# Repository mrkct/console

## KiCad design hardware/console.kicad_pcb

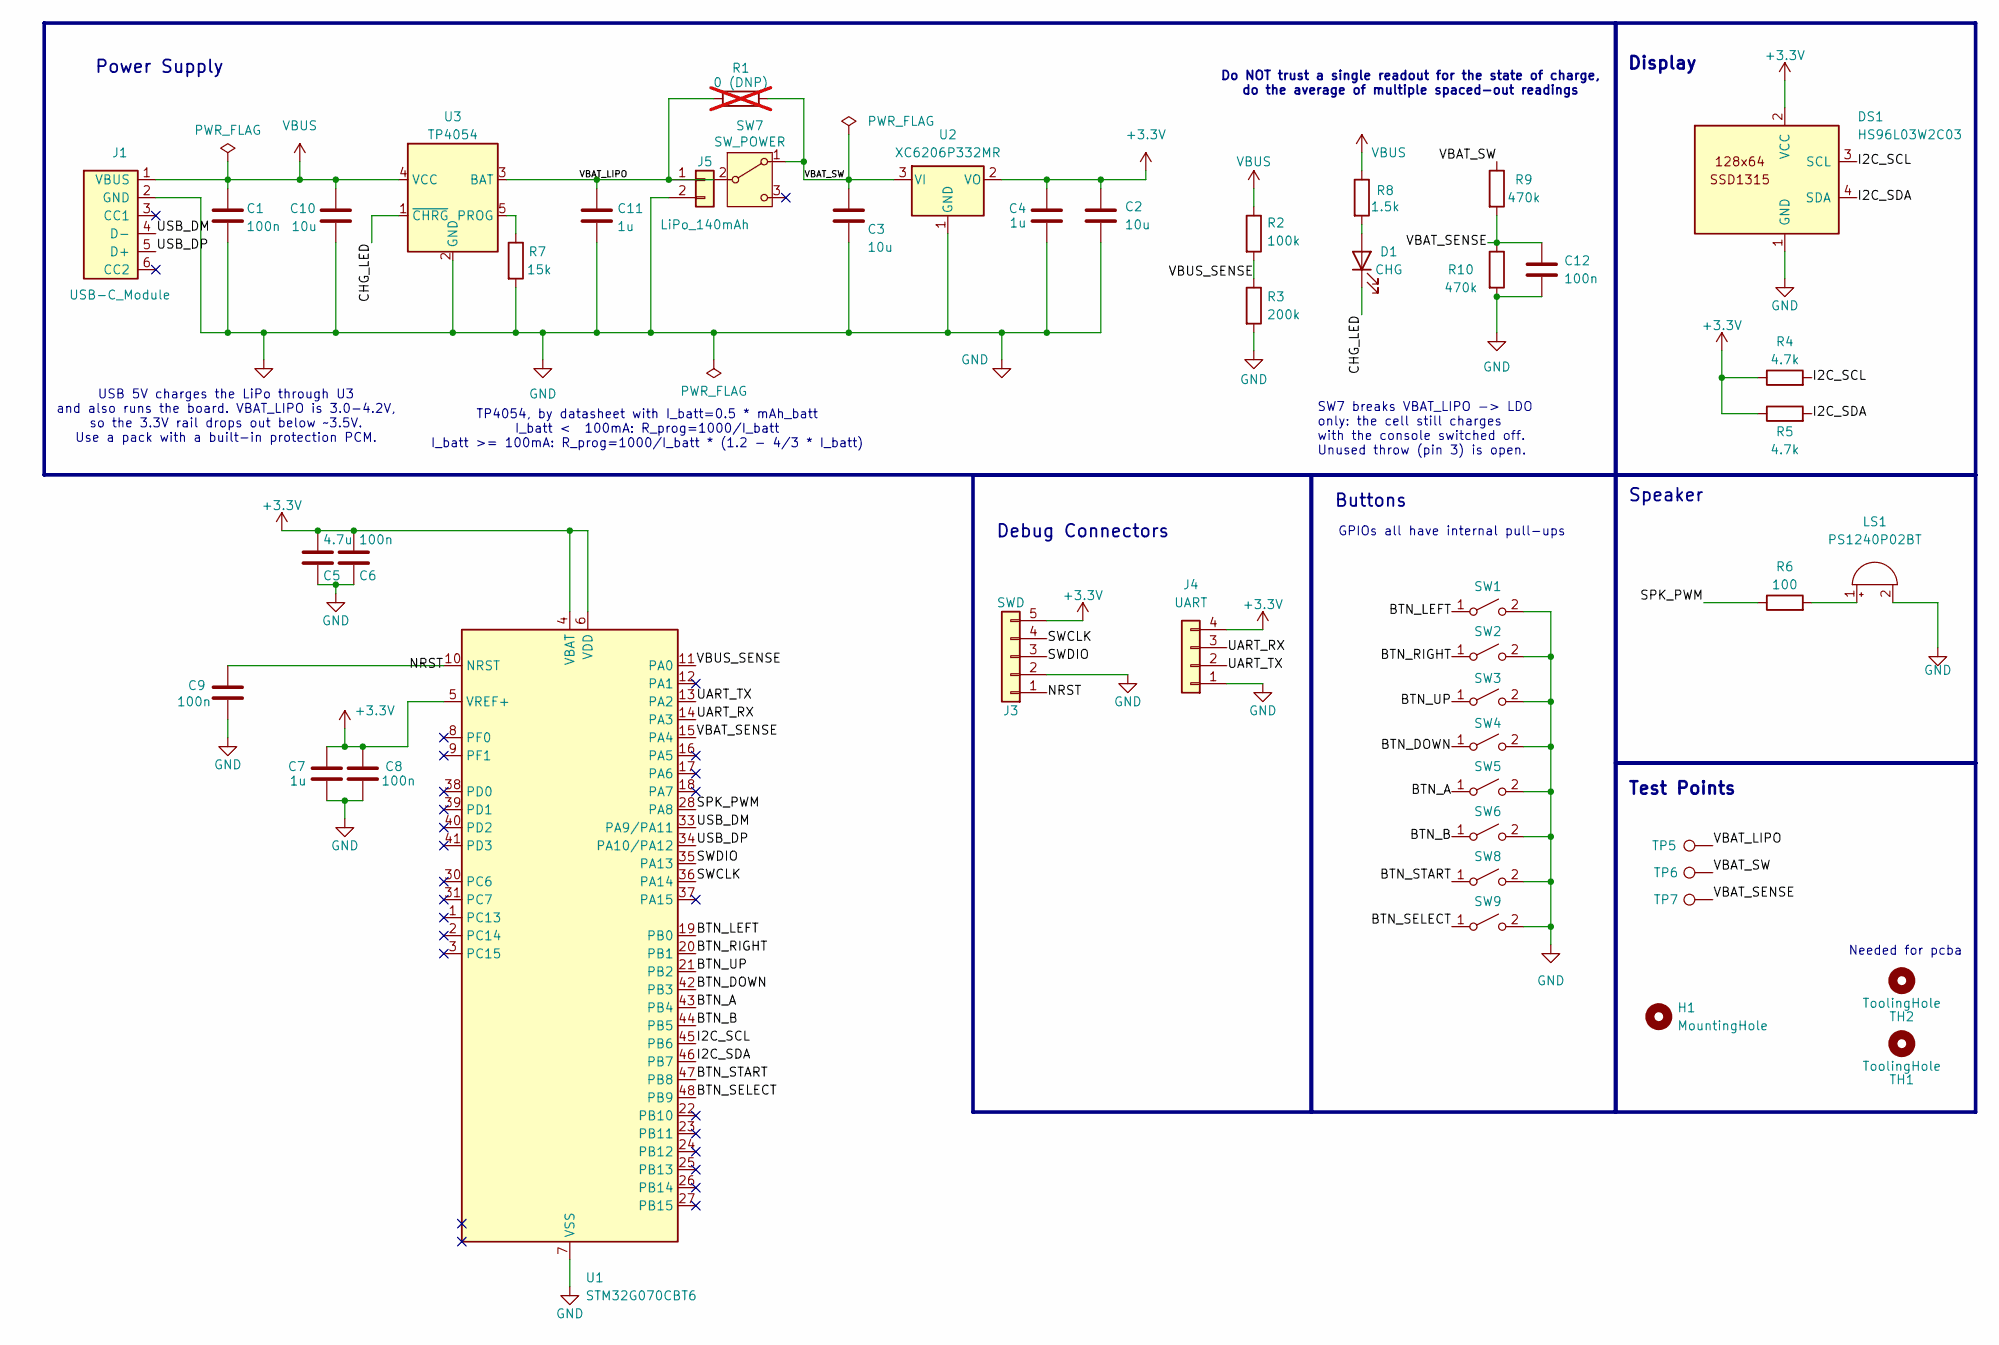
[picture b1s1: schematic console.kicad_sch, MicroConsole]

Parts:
C1, C6, C8, C9, C12: 100n; C_0402_1005Metric; Voltage 16V; MPN CL05B104KO5NNNC; LCSC C1525
C2, C3, C10: 10u; C_0805_2012Metric; Voltage 25V; MPN CL21A106KAYNNNE; LCSC C15850
C4, C7, C11: 1u; C_0402_1005Metric; Voltage 25V; MPN CL05A105KA5NQNC; LCSC C52923
C5: 4.7u; C_0603_1608Metric; Voltage 16V; MPN CL10A475KO8NNNC; LCSC C19666
D1: CHG; LED_0603_1608Metric; MPN KT-0603R; LCSC C2286
DS1: HS96L03W2C03; OLED-TH_L27.8-W27.2-P2.54_C9900033791; LCSC C5248080
H1: MountingHole; MountingHole_2.1mm
J1: USB-C_Module; USBC-TH_L21.6-W12.8-P2.54
J3: SWD; PinHeader_1x05_P2.54mm_Vertical
J4: UART; PinHeader_1x04_P2.54mm_Vertical
J5: LiPo_140mAh; JST_PH_S2B-PH-K_1x02_P2.00mm_Horizontal; MPN BX-PH2.0-2PZZ; LCSC C18077744
LS1: PS1240P02BT; Buzzer_TDK_PS1240P02BT_D12.2mm_H6.5mm; MPN PS1240P02BT; LCSC C76871
R1: 0 (DNP); R_0402_1005Metric; not fitted
R2: 100k; R_0402_1005Metric; Tolerance 1%; MPN 0402WGF1003TCE; LCSC C25741
R3: 200k; R_0402_1005Metric; Tolerance 1%; MPN 0402WGF2003TCE; LCSC C25764
R4, R5: 4.7k; R_0402_1005Metric; Tolerance 1%; MPN 0402WGF4701TCE; LCSC C25900
R6: 100; R_0402_1005Metric; Tolerance 1%; MPN 0402WGF1000TCE; LCSC C25076
R7: 15k; R_0402_1005Metric; Tolerance 1%; MPN 0402WGF1502TCE; LCSC C25756
R8: 1.5k; R_0402_1005Metric; Tolerance 1%; MPN 0402WGF1501TCE; LCSC C25867
R9, R10: 470k; R_0603_1608Metric; Tolerance 1%; MPN 0603WAF4703T5E; LCSC C23178
SW1, SW2, SW3, SW4, SW5, SW6, SW8, SW9: SW_PUSH; SW_SPST_TS-1088-xR020; LCSC C720477
SW7: SW_POWER; SW-TH_L8.5-W3.5-P2.50-D0.9; MPN SS-12D00
TH1, TH2: ToolingHole; TOOL-NPTH-D1.152
TP5: VBAT_LIPO; TestPoint_THTPad_D1.5mm_Drill0.7mm
TP6: VBAT_SW; TestPoint_THTPad_D1.5mm_Drill0.7mm
TP7: VBAT_SENSE; TestPoint_THTPad_D1.5mm_Drill0.7mm
U1: STM32G070CBT6; LQFP-48_7x7mm_P0.5mm; MPN STM32G070CBT6; LCSC C529338
U2: XC6206P332MR; SOT-23-3; MPN XC6206P332MR-G; LCSC C5446
U3: TP4054; SOT-23-5; MPN TP4054-42-SOT25R; LCSC C32574

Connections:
+3.3V: C2.1, C4.1, C5.1, C6.1, C7.1, C8.1, DS1.2 (VCC), J3.5, J4.4, R4.1, R5.1, U1.4 (VBAT), U1.5 (VREF+), U1.6 (VDD), U2.2 (VO)
/BTN_A: SW5.1 (A), U1.43 (PB4)
/BTN_B: SW6.1 (A), U1.44 (PB5)
/BTN_DOWN: SW4.1 (A), U1.42 (PB3)
/BTN_LEFT: SW1.1 (A), U1.19 (PB0)
/BTN_RIGHT: SW2.1 (A), U1.20 (PB1)
/BTN_SELECT: SW9.1 (A), U1.48 (PB9)
/BTN_START: SW8.1 (A), U1.47 (PB8)
/BTN_UP: SW3.1 (A), U1.21 (PB2)
/CHG_LED: D1.1 (K), U3.1 (~CHRG)
/I2C_SCL: DS1.3 (SCL), R4.2, U1.45 (PB6)
/I2C_SDA: DS1.4 (SDA), R5.2, U1.46 (PB7)
/NRST: C9.1, J3.1, U1.10 (NRST)
/SPK_PWM: R6.1, U1.28 (PA8)
/SWCLK: J3.4, U1.36 (PA14)
/SWDIO: J3.3, U1.35 (PA13)
/UART_RX: J4.3, U1.14 (PA3)
/UART_TX: J4.2, U1.13 (PA2)
/USB_DM: J1.4 (D-), U1.33 (PA9/PA11)
/USB_DP: J1.5 (D+), U1.34 (PA10/PA12)
/VBAT_LIPO: C11.1, J5.1, R1.1, SW7.2 (B), TP5.1 (1_1), U3.3 (BAT)
/VBAT_SENSE: C12.1, R9.2, R10.1, TP7.1 (1_1), U1.15 (PA4)
/VBAT_SW: C3.1, R1.2, R9.1, SW7.1 (A), TP6.1 (1_1), U2.3 (VI)
/VBUS_SENSE: R2.2, R3.1, U1.11 (PA0)
GND: C1.2, C2.2, C3.2, C4.2, C5.2, C6.2, C7.2, C8.2, C9.2, C10.2, C11.2, C12.2, DS1.1 (GND), J1.2 (GND), J3.2, J4.1, J5.2, LS1.2 (-), R3.2, R7.2, R10.2, SW1.2 (B), SW2.2 (B), SW3.2 (B), SW4.2 (B), SW5.2 (B), SW6.2 (B), SW8.2 (B), SW9.2 (B), U1.7 (VSS), U2.1 (GND), U3.2 (GND)
unnamed: D1.2 (A), R8.2
unnamed: LS1.1 (+), R6.2
unnamed: R7.1, U3.5 (PROG)
VBUS: C1.1, C10.1, J1.1 (VBUS), R2.1, R8.1, U3.4 (VCC)

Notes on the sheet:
GPIOs all have internal pull-ups
Do NOT trust a single readout for the state of charge, do the average of multiple spaced-out readings
TP4054, by datasheet with I_batt=0.5 * mAh_batt I_batt < 100mA: R_prog=1000/I_batt I_batt >= 100mA: R_prog=1000/I_batt * (1.2 - 4/3 * I_batt)
USB 5V charges the LiPo through U3 and also runs the board. VBAT_LIPO is 3.0-4.2V, so the 3.3V rail drops out below ~3.5V. Use a pack with a built-in protection PCM.
Debug Connectors
Needed for pcba
Power Supply
Buttons
Test Points
Speaker
SW7 breaks VBAT_LIPO -> LDO only: the cell still charges with the console switched off. Unused throw (pin 3) is open.
Display

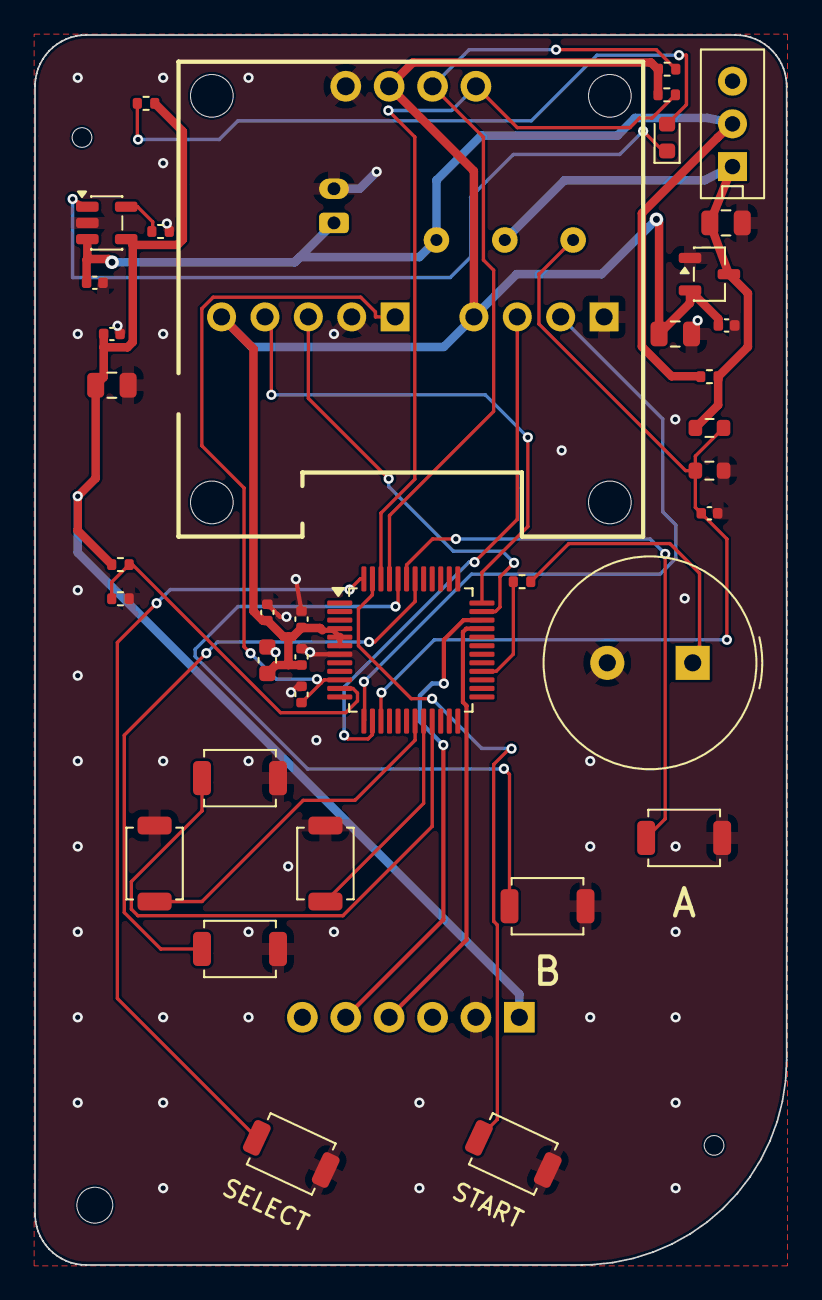
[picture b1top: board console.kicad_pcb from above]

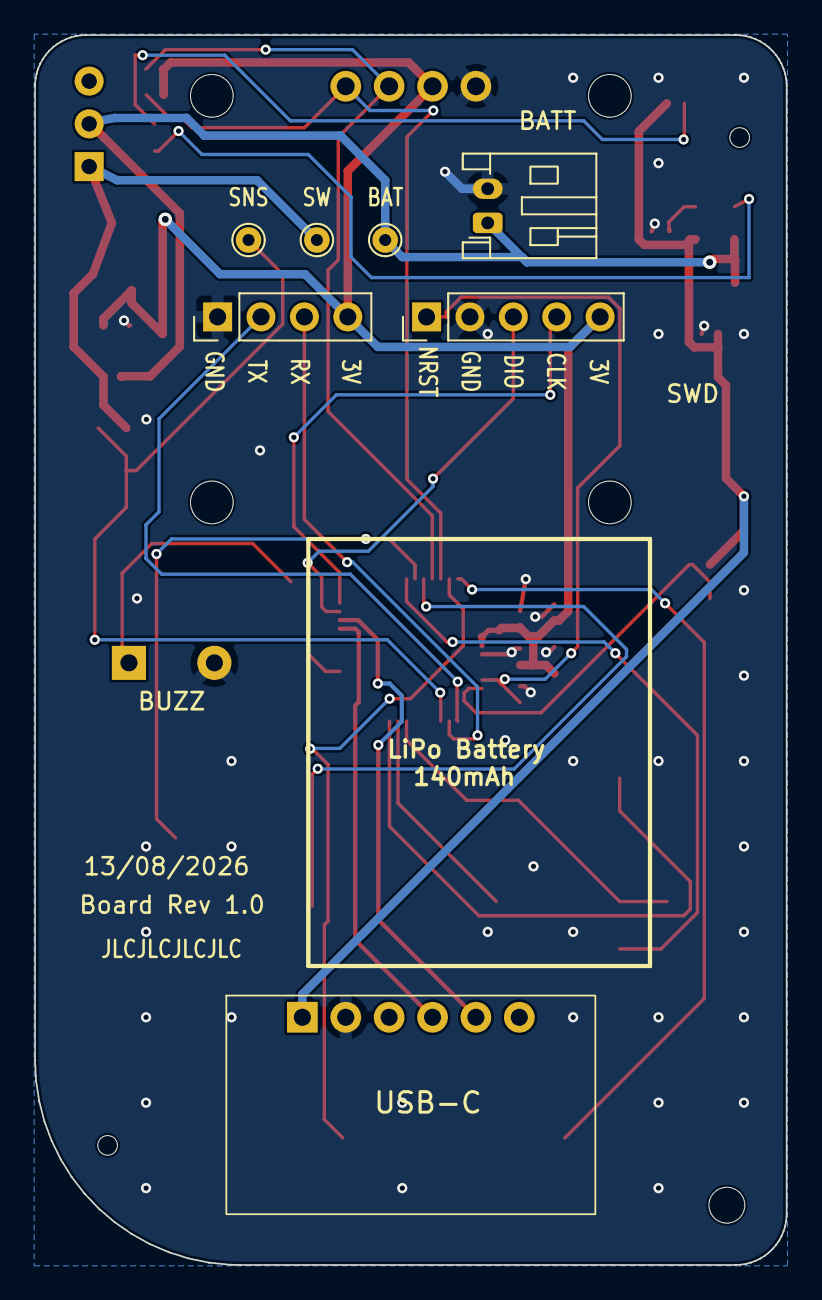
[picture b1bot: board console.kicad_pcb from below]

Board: 2 copper layers, 44.0 x 72.0 mm, 47 parts (7 on the bottom side), 29 nets.

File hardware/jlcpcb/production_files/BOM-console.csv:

Comment,Designator,Footprint,LCSC,Quantity
1.5k,R8,R_0402_1005Metric,C25867,1
100,R6,R_0402_1005Metric,C25076,1
100k,R2,R_0402_1005Metric,C25741,1
100n,"C1,C12,C6,C8,C9",C_0402_1005Metric,C1525,5
10u,"C10,C2,C3",C_0805_2012Metric,C15850,3
15k,R7,R_0402_1005Metric,C25756,1
1u,"C11,C4,C7",C_0402_1005Metric,C52923,3
200k,R3,R_0402_1005Metric,C25764,1
4.7k,"R4,R5",R_0402_1005Metric,C25900,2
4.7u,C5,C_0603_1608Metric,C19666,1
470k,"R10,R9",R_0603_1608Metric,C23178,2
CHG,D1,LED_0603_1608Metric,C2286,1
STM32G070CBT6,U1,LQFP-48_7x7mm_P0.5mm,C529338,1
SW_PUSH,"SW1,SW2,SW3,SW4,SW5,SW6,SW8,SW9",SW_SPST_TS-1088-xR020,C720477,8
TP4054,U3,SOT-23-5,C32574,1
XC6206P332MR,U2,SOT-23-3,C5446,1

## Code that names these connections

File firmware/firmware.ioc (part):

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Mcu.Name=STM32G0B1C(B-C-E)Tx
Mcu.Package=LQFP48
Mcu.UserName=STM32G0B1CBTx
PA0.Mode=SYS_WakeUp0
PA0.Signal=SYS_WKUP1
PA11\ [PA9].Mode=Device
PA11\ [PA9].Signal=USB_DM
PA12\ [PA10].Mode=Device
PA12\ [PA10].Signal=USB_DP
PA13.Mode=Serial_Wire
PA13.Signal=SYS_SWDIO
PA14-BOOT0.Mode=Serial_Wire
PA14-BOOT0.Signal=SYS_SWCLK
PA2.GPIOParameters=GPIO_Label
PA2.GPIO_Label=UART_TX
PA2.Mode=Asynchronous
PA2.Signal=USART2_TX
PA3.GPIOParameters=GPIO_Label
PA3.GPIO_Label=UART_RX
PA3.Mode=Asynchronous
PA3.Signal=USART2_RX
PA4.GPIOParameters=GPIO_Label
PA4.GPIO_Label=VBAT_SENSE
PA4.Mode=IN4
PA4.Signal=ADC1_IN4
PA8.GPIOParameters=GPIO_Label
PA8.GPIO_Label=SPK_PWM
PA8.Signal=S_TIM1_CH1
PB0.GPIOParameters=GPIO_PuPd,GPIO_Label
PB0.GPIO_Label=BTN_LEFT
PB0.GPIO_PuPd=GPIO_PULLUP
PB0.Signal=GPIO_Input
PB1.GPIOParameters=GPIO_PuPd,GPIO_Label
PB1.GPIO_Label=BTN_RIGHT
PB1.GPIO_PuPd=GPIO_PULLUP
PB1.Signal=GPIO_Input
PB2.GPIOParameters=GPIO_PuPd,GPIO_Label
PB2.GPIO_Label=BTN_UP
PB2.GPIO_PuPd=GPIO_PULLUP
PB2.Signal=GPIO_Input
PB3.GPIOParameters=GPIO_PuPd,GPIO_Label
PB3.GPIO_Label=BTN_DOWN
PB3.GPIO_PuPd=GPIO_PULLUP
PB3.Signal=GPIO_Input
PB4.GPIOParameters=GPIO_PuPd,GPIO_Label
PB4.GPIO_Label=BTN_A
PB4.GPIO_PuPd=GPIO_PULLUP
PB4.Signal=GPIO_Input
PB5.GPIOParameters=GPIO_PuPd,GPIO_Label
PB5.GPIO_Label=BTN_B
PB5.GPIO_PuPd=GPIO_PULLUP
PB5.Signal=GPIO_Input
PB6.Mode=I2C
PB6.Signal=I2C1_SCL
PB7.Mode=I2C
PB7.Signal=I2C1_SDA
PB8.GPIOParameters=GPIO_PuPd,GPIO_Label
PB8.GPIO_Label=BTN_START
PB8.GPIO_PuPd=GPIO_PULLUP
PB8.Signal=GPIO_Input
PB9.GPIOParameters=GPIO_PuPd,GPIO_Label
PB9.GPIO_Label=BTN_SELECT
PB9.GPIO_PuPd=GPIO_PULLUP
PB9.Signal=GPIO_Input
RCC.HSE_VALUE=8000000
RCC.SYSCLKFreq_VALUE=16000000
board=custom
